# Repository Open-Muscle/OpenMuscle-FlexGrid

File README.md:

# 🧠 OpenMuscle-FlexGrid

OpenMuscle FlexGrid is a modular 60-sensor pressure-sensing platform designed for advanced forearm-based gesture tracking and biomechanical research.

This device is part of the [OpenMuscle](https://github.com/Open-Muscle) ecosystem and represents a leap forward from the original 12-sensor OM12 prototype by introducing high-density, flex-rigid PCBs and better sensor modularity.

### 📌 For documentation, firmware, and assembly guidance, visit the [OpenMuscle Hub](https://github.com/Open-Muscle/OpenMuscle-Hub).

---

## 🚀 Current revisions

**V4 (current, validated).** Fabricated at JLCPCB in June 2026 (10-unit batch, single-side SMT), brought up 2026-06-23 and in use since. Two V4 bands were assembled, flashed with [FlexGridV4-Firmware](https://github.com/Open-Muscle/FlexGridV4-Firmware) v4.0.1 and shipped as the first OpenMuscle starter kit in October 2026. V4 is the best-performing FlexGrid revision to date and the one to build. It adds an on-device **microSD card socket** for local data logging, a **discrete RGB status LED** on three PWM channels, and a reoriented slimmer board profile that hugs the forearm. It carries forward the V3 power and interconnect architecture, with the FFC tail width corrected from 11.1 mm to **10.5 mm** per the Wurth 687120183722 datasheet, the ADC matrix-row caps reduced from 2.2 uF to **100 pF** (resolves V3's 22 ms RC bleed in silicon rather than via post-fab cap removal), all resistors normalized to 0603, and several footprint cleanups. Manufacturing strategy: **single-side SMT at JLCPCB plus hand-soldering of bottom-side parts and through-hole connectors**. The design files are now at board revision **V4-2** (2026-11-03): USB presence sensing for the firmware, vias moved out of the SMD pads, USB data lines re-routed as a pair. V4-2 has not been fabricated yet, and its BOM, placement and Gerber files are still the June 2026 as-ordered set. Full status, bring-up findings and the fab checklist are in the [V4 README](KiCad/OM-FlexGrid%20V4/README.md).

**V3 (previous, validated 2026-05-13).** First revision to use a 20-pin ZIF FFC connector for the flex-to-rigid interconnect (Wurth 687120183722). Two boards populated and tested end-to-end. Sensor matrix delivers **clean single-cell press detection across all 60 sensors** with ~22% carryover decaying to noise floor within 3 columns. **V3 is the first FlexGrid generation usable as a real ML training data source.** Firmware: [FlexGridV3-Firmware v0.1.7](https://github.com/Open-Muscle/FlexGridV3-Firmware).

→ For V4 hardware files, see [`KiCad/OM-FlexGrid V4/`](KiCad/OM-FlexGrid%20V4/) and the [V4 README](KiCad/OM-FlexGrid%20V4/README.md). For V3 see [`KiCad/OM-FlexGrid V3/`](KiCad/OM-FlexGrid%20V3/) and the [V3 README](KiCad/OM-FlexGrid%20V3/README.md). Firmware: V4 bands run [FlexGridV4-Firmware](https://github.com/Open-Muscle/FlexGridV4-Firmware); V3 boards run [FlexGridV3-Firmware](https://github.com/Open-Muscle/FlexGridV3-Firmware).

| Revision | Status | Notes |
|----------|--------|-------|
| **V4** | 🟢 Validated (current) | microSD + RGB LED + slimmer reorient; 10.5 mm FFC tail; 100 pF ADC caps; fabbed 2026-06, in starter kits since 2026-10; design files at V4-2 (USB sensing, vias out of pads, USB pair; not yet fabbed) |
| **V3** | 🟢 Validated (previous) | 20-pin FFC interconnect, integrated stiffened FFC tail, ~140 Hz raw scan |
| V2 | 🟢 Tested | FFC connector exploration, fabric harness testing |
| V1 | 🟢 Tested | First production revision |
| V0 | 🟢 Tested | Original prototype |

→ Full cross-version comparison: [`KiCad/REVISIONS.md`](KiCad/REVISIONS.md). Manufacturing process used across revisions: [`docs/JLCPCB_WORKFLOW.md`](docs/JLCPCB_WORKFLOW.md).

---

## 🧬 Overview

FlexGrid uses a flexible pressure sensor matrix with rigid breakout interfaces to detect volumetric muscle contractions in real time. It supports:

- 🧠 Biomechanical signal analysis  
- 🦾 Prosthetics and exosuit research  
- 🎛️ Machine learning data pipelines  

---

## 📁 Hardware Design Files

Design files are organized by board type and version:

### 🔌 KiCad Schematics & PCB Layout

📂 [`KiCad/`](KiCad/) — all design files, organized by revision.

| Revision | Path | Description |
|----------|------|-------------|
| **V4** (current) | [`KiCad/OM-FlexGrid V4/`](KiCad/OM-FlexGrid%20V4/) | Validated. microSD socket, RGB status LED, slimmer reorient, 10.5 mm FFC tail, 100 pF ADC caps. See [V4 README](KiCad/OM-FlexGrid%20V4/README.md). |
| **V3** (previous) | [`KiCad/OM-FlexGrid V3/`](KiCad/OM-FlexGrid%20V3/) | Validated. 20-pin ZIF FFC interconnect. See [V3 README](KiCad/OM-FlexGrid%20V3/README.md). |
| V2 | [`KiCad/OM-FlexGrid V2/`](KiCad/OM-FlexGrid%20V2/) | Tested. FFC exploration + fabric harness. See [V2 README](KiCad/OM-FlexGrid%20V2/README.md). |
| V1 | [`KiCad/OM-FlexGrid V1/`](KiCad/OM-FlexGrid%20V1/) | First production revision. |
| V0 | [`KiCad/OM-FlexGrid V0/`](KiCad/OM-FlexGrid%20V0/) | Original prototype. |

Each revision folder contains both the flex (`OM-FlexGrid-Flex/`) and rigid (`OM-FlexGrid-Rigid-PCB/`) board projects, plus their gerber bundles.

---

### 📦 Bill of Materials

BOMs live next to their KiCad project for each revision:

- **V4 Rigid (JLCPCB-ready):** [`KiCad/OM-FlexGrid V4/OM-FlexGrid-Rigid-PCB/jlcpcb/production_files/BOM-OM-FlexGrid-Rigid-PCB.csv`](KiCad/OM-FlexGrid%20V4/OM-FlexGrid-Rigid-PCB/jlcpcb/production_files/BOM-OM-FlexGrid-Rigid-PCB.csv) (LCSC part numbers, machine-readable, generated by the JLCPCB KiCad plugin). This is the June 2026 as-ordered V4 set; the V4-2 additions (R19, R20, R21) are not in it yet. The hand-soldered parts list (microSD socket, FFC connector, battery JST, pin headers, plus single-side-strategy BOT-side SMT) is documented prose-style in the [V4 README](KiCad/OM-FlexGrid%20V4/README.md#hand-soldered-parts-full-list).
- **V3 Rigid:** [`KiCad/OM-FlexGrid V3/OM-FlexGrid-Rigid-PCB/OM-FlexGrid-Rigid-PCB.csv`](KiCad/OM-FlexGrid%20V3/OM-FlexGrid-Rigid-PCB/OM-FlexGrid-Rigid-PCB.csv) (KiCad export).
- **Flex (V3 and V4):** no electronic-component BOM. The flex tail integrates the FFC connector pads directly; the only off-board parts are the Velostat sheet and the mating Wurth 687120183722 connector populated on the rigid board.

Older revision BOMs are kept under [`BOM/`](BOM/) for history.

---

### 🛠 Assembly & Testing

For V4: the [build video](https://youtu.be/2tb6GW4FNU0) covers hand-soldering the parts JLCPCB does not populate, [BRINGUP.md](https://github.com/Open-Muscle/FlexGridV4-Firmware/blob/main/BRINGUP.md) in the firmware repo covers flashing, and the [band reference](https://github.com/Open-Muscle/FlexGridV4-Firmware/blob/main/docs/device-reference.md) explains every button and light pattern. Recording, training and inference software lives in [OpenMuscle-Software](https://github.com/Open-Muscle/OpenMuscle-Software). For the wider picture see the [OpenMuscle Hub](https://github.com/Open-Muscle/OpenMuscle-Hub) and the videos on [YouTube Open Muscle](https://youtube.com/@openmuscle) or [TURFPTAx Youtube](https://youtube.com/@turfptax).

---

## 🤝 Contributions

We welcome improvements to sensor design, firmware, or real-world testing. Please fork the repo and submit pull requests!

---
**Open Muscle** is an open-source prosthetic sensor initiative designed for accessibility, innovation, and community collaboration.

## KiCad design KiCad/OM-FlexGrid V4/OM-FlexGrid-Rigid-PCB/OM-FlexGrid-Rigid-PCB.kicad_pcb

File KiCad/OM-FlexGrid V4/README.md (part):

# OM-FlexGrid V4

> **Status: VALIDATED, CURRENT REVISION.** Brought up 2026-06-23 from the 10-unit JLCPCB batch and in use since. Two bands were assembled, flashed with [FlexGridV4-Firmware](https://github.com/Open-Muscle/FlexGridV4-Firmware) v4.0.1 and shipped as the first OpenMuscle starter kit in October 2026. V4 is the best-performing FlexGrid revision to date. Two hardware bugs surfaced during bring-up: USBLC6 ESD chip pinout reversed in the schematic (fixed in the schematic; the June boards work with a 180-degree chip rotation), and the as-ordered IMU is a TOKMAS rebrand rather than genuine InvenSense as planned (driver auto-probes both variants; see [Bring-up findings](#bring-up-findings-2026-06-23) below). Total landed cost $341.84 for 10 units (~$35 per board for the JLC half; see [Cost breakdown](#cost-breakdown-10-unit-batch-june-2026) for per-unit details).
>
> **Design files are at revision V4-2 (2026-11-03).** V4-2 adds USB presence sensing, moves the vias out of the SMD pads and re-routes the USB data lines as a pair; see [Revision V4-2](#revision-v4-2-2026-11-03). V4-2 has not been fabricated. The BOM, CPL and Gerber files under `jlcpcb/` and `production/` are still the June 2026 as-ordered V4 set and must be regenerated before the next order.

## 🎬 Build video

[**Unboxing & Setup: assembling the FlexGrid V4**](https://youtu.be/2tb6GW4FNU0) walks through hand-soldering the parts JLCPCB does not populate (ESP32-S3 module, CD74HC4067 mux, ZIF/FFC connector, USB-C, buttons, RGB LED), the USBLC6 180-degree rotation fix, and first power-on with the flex sensor mated. The microSD socket and haptic parts are deferred to a future video.

## 📄 Design documents (PDFs)

For people who want to review the design without opening KiCad:

### Rigid PCB

- 📐 [`FlexGridV4-Rigid-Schematic.pdf`](OM-FlexGrid-Rigid-PCB/FlexGridV4-Rigid-Schematic.pdf): full schematic, all sheets, all nets named
- 🟦 [`FlexGridV4-Rigid-PCB.pdf`](OM-FlexGrid-Rigid-PCB/FlexGridV4-Rigid-PCB.pdf): board layout

### Flex PCB

- 📐 [`FlexGridV4-Flex-Schematic.pdf`](OM-FlexGrid-Flex/FlexGridV4-Flex-Schematic.pdf): sensor matrix schematic
- 🟦 [`FlexGridV4-Flex-PCB.pdf`](OM-FlexGrid-Flex/FlexGridV4-Flex-PCB.pdf): flex layout including the stiffened FFC tail
- 🟧 [`FrontCopper_SolderMask.pdf`](OM-FlexGrid-Flex/FrontCopper_SolderMask.pdf): front-side copper + soldermask overlay (useful for sanity-checking the Velostat sensor cell exposures)

### What gets populated and what doesn't

The split between "JLCPCB assembles this" and "I hand-solder this after the boards arrive" is documented in [Hand-soldered parts (full list)](#hand-soldered-parts-full-list) below. tl;dr:

- **JLCPCB assembles all TOP-side SMT parts** (passives, regulators, charger, MUX-driver MOSFETs, MAX16054, USBLC6, IMU, CHRG LED, RGB LED, etc.)
- **You hand-solder everything else**: all BOT-side SMT (including U1 CD74HC4067 mux and U2 ESP32-S3 module), the microSD socket, the Wurth FFC connector, USB-C, and every through-hole pin header / JST. The per-designator table further down has each part listed by reference designator with solder-difficulty notes.

Fourth major revision of the Open Muscle FlexGrid wearable sensor platform. V4 builds on the V3 production baseline (which validated the FFC interconnect and proved the 60-cell matrix as a usable ML training data source) and adds on-device storage, a status indicator, and a slimmer board profile.

---

## Bring-up findings (2026-06-23)

Two boards from the 10-unit fab batch were flashed with V4 MicroPython firmware ([Open-Muscle/FlexGridV4-Firmware](https://github.com/Open-Muscle/FlexGridV4-Firmware), see its `BRINGUP.md` for step-by-step flashing instructions). Both ran the OpenMuscle discovery + subscribe protocol end-to-end against the PC `openmuscle web` app and the Android Connect client. Two hardware bugs surfaced during bring-up; both are documented here so future builders do not re-discover them.

### 1. USBLC6-2SC6 pinout reversed in schematic (FIXED)

The V4 KiCad schematic wired the USBLC6 with pin 2 on VBUS and pin 5 on GND. The actual chip pinout is the other way around (pin 2 = GND, pin 5 = VCC). With the silkscreen-correct placement, USB enumerates VBUS only (Windows reports "Device Descriptor Request Failed"), no COM port appears.

- **Workaround for the existing 10-unit batch:** rotate the USBLC6 chip 180 degrees from the silkscreen orientation during placement. The SOT-23-6 footprint is symmetric so the I/O pin pairs still route correctly, and VCC and GND land where they belong.
- **Schematic fix landed** in this repo. The next fab order will be correct without rotation.

### 2. IMU is a TOKMAS rebrand, not genuine InvenSense (DRIVER WORKAROUND)

The pre-fab checklist documented the IMU choice as genuine InvenSense ICM-42688-P (LCSC C1850418). The as-ordered BOM ended up with the cheaper TOKMAS rebrand (LCSC C54308212) instead. TOKMAS has the same general silicon spec but a different I2C address (0x36 / 0x37 instead of 0x68 / 0x69) and a different register map (data at 0x00-0x0D instead of 0x1F-0x2A).

- **Workaround:** [`lib/imu.py`](https://github.com/Open-Muscle/FlexGridV4-Firmware/blob/main/lib/imu.py) in the V4 firmware auto-probes both variants. Verified working on board #1: live accel + gyro at the expected rates.
- **Recommendation for the next fab order:** switch back to genuine InvenSense (C1850418) and retire the TOKMAS code path. The ~$11 per-chip savings cost a custom driver branch and ongoing maintenance.

### Firmware repo and bring-up guide

- Firmware: [Open-Muscle/FlexGridV4-Firmware](https://github.com/Open-Muscle/FlexGridV4-Firmware)
- Step-by-step flashing instructions: [`BRINGUP.md`](https://github.com/Open-Muscle/FlexGridV4-Firmware/blob/main/BRINGUP.md)
- One-shot flash script: `flash.py COM<port>` after pip-installing esptool 5.x + mpremote and downloading the MicroPython binary

---

## Revision V4-2 (2026-11-03)

Schematic and layout changes made after the first production run. These live in the KiCad files only: nothing at V4-2 has been fabricated, and the `jlcpcb/` and `production/` outputs are still the June 2026 as-ordered set. Rev field in the schematic title block: `V4-2`.

### USB presence sensing (new)

The June boards cannot tell whether USB is plugged in. The MAX16054 latch keeps the board powered while VBUS is present, so the power button appears to do nothing on USB and the firmware has no way to know why (see the [band reference](https://github.com/Open-Muscle/FlexGridV4-Firmware/blob/main/docs/device-reference.md) in the firmware repo). V4-2 adds a VBUS divider the ESP32-S3 can read.

| Designator | Value | Footprint | Between | Role |
|---|---|---|---|---|
| R19 | 10k | 0603 | VBUS and `VBUS-STAT` | high side of the VBUS sense divider |
| R20 | 100k | 0603 | `VBUS-STAT` and GND | low side of the divider |
| R21 | 100k | 0603 | `PWR_OFF` and GND | pull-down on the Q3 gate (IO45) so the power-off MOSFET stays off while the ESP32 boots |

`VBUS-STAT` lands on U2 pin 32 (IO39). **Value check still open:** as drawn, 10k over 100k puts about 4.5 V on IO39 with 5 V on VBUS, above the ESP32-S3 GPIO limit. Pick values that keep the node under 3.3 V (for example 100k over 100k for 2.5 V) before the next fab. Firmware support for reading the pin is not written yet.

The charger PROG note on the schematic was also corrected: R4 is 2k on the STC4054 PROG pin, which sets the charge current to 500 mA (the old note suggesting 2.7k was stale).

### Vias moved out of the pads ([#3](https://github.com/Open-Muscle/OpenMuscle-FlexGrid/issues/3))

The June layout had 29 vias sitting inside SMD pads (ESP32 module pads, mux, LDO, charger, buttons, microSD socket, several resistors). An unplugged via inside a pad wicks solder away from the joint during reflow. V4-2 moves them next to their pads instead. One remains, on Q3 pad 2 (GND, source of the power-off MOSFET), where the via annulus still overlaps the pad edge.

### USB data lines routed as a pair ([#4](https://github.com/Open-Muscle/OpenMuscle-FlexGrid/issues/4))

The June layout ran D+ and D- between the USBLC6 and the ESP32 module as two unrelated traces, 15.6 mm and 34.5 mm long. V4-2 routes them together: 16.4 mm and 19.6 mm, 0.2 mm wide, 0.25 mm edge gap where they run side by side, one layer change each; the connector-to-ESD segments are 7.6 mm and 7.3 mm. The pair uses the default net class geometry and has not been checked against the JLCPCB 4-layer stack-up for 90 ohm differential impedance. The ESP32-S3 is a USB full-speed device (12 Mbit/s), so over this length the change is about tidiness and skew rather than a hard signal-integrity requirement.

---

## What is new in V4 vs V3

| Area | V3 | V4 | Why |
|---|---|---|---|
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
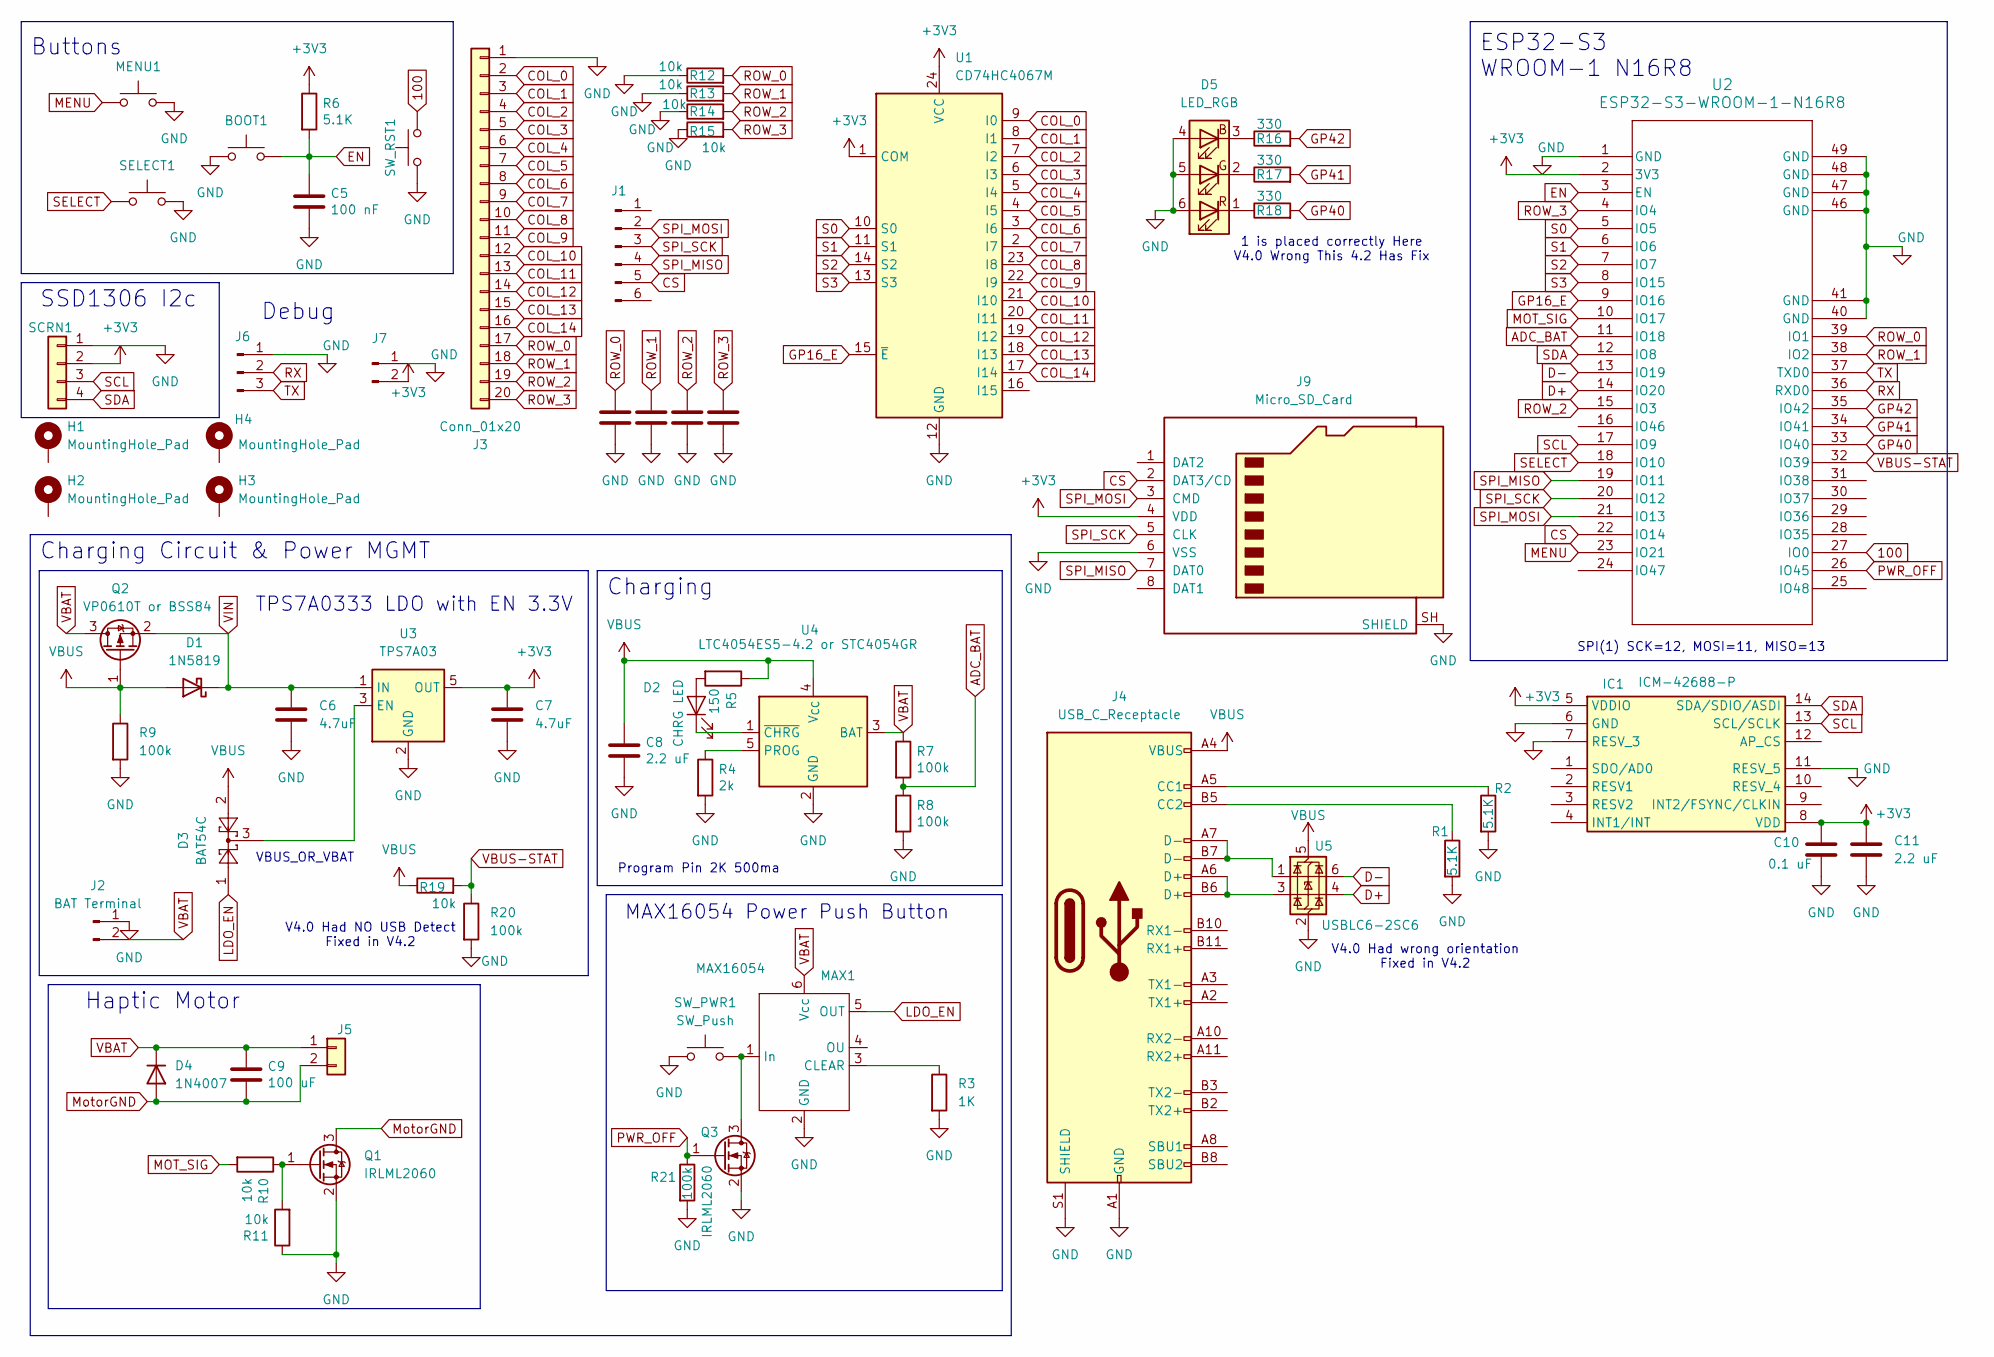
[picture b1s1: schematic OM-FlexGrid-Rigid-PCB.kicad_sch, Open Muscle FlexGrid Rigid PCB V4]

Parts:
BOOT1: SW_Push; EVQP2P02M; LCSC C512395
C5: 100 nF; C_0603_1608Metric; JLCPN C1525
C6, C7: 4.7uF; C_0805_2012Metric; LCSC C1779
C8: 2.2 uF; C_0603_1608Metric; JLCPN C12530
C9: 100 uF; C_0603_1608Metric; JLCPN C12530
C10: 0.1 uF; C_0603_1608Metric; LCSC C14663
C11: 2.2 uF; C_0603_1608Metric; LCSC C23630
C12, C13, C14, C15: 100 pF; C_0603_1608Metric; JLCPN C12530
D1: 1N5819; D_SOD-123; LCSC C64885
D2: CHRG LED; LED_0805_2012Metric; JLCPN C72043
D3: BAT54C; SOT-23; LCSC C22466350
D4: 1N4007; D_SOD-123; LCSC C22440662
D5: LED_RGB; LED_RGB_PLCC-6; LCSC C2827305
H1, H2, H3, H4: MountingHole_Pad; MountingHole_2.2mm_M2
IC1: ICM-42688-P; LGA-14_3x2.5mm_P0.5mm_LayoutBorder3x4y; Mouser Part Number 410-ICM-42688-P
J1: Conn_01x06_Pin; PinHeader_2x03_P1.27mm_Vertical
J2: BAT Terminal; PinHeader_1x02_P2.54mm_Vertical
J3: Conn_01x20; 687120183722-20P-Bottom
J4: USB_C_Receptacle; USB_C_Receptacle_HRO_TYPE-C-31-M-12
J5: Conn_01x02; PinHeader_1x02_P2.00mm_Vertical
J6: Conn_01x03_Pin; PinHeader_1x03_P2.54mm_Vertical
J7: Conn_01x02_Pin; PinSocket_1x02_P2.00mm_Vertical
J9: Micro_SD_Card; CONN_503398-1892_MOL
MAX1: MAX16054; TSOT-23-6; LCSC C79401
MENU1: SW_Push; EVQP2P02M; LCSC C512395
Q1, Q3: IRLML2060; SOT-23; LCSC C67275
Q2: VP0610T or BSS84; SOT-23; LCSC C8492
R1, R2, R6: 5.1K; R_0603_1608Metric; JLCPN C25905
R3: 1K; R_0603_1608Metric; LCSC C21190
R4: 2k; R_0603_1608Metric; JLCPN C25905
R5: 150; R_0603_1608Metric; JLCPN C4109
R7, R8: 100k; R_0603_1608Metric; JLCPN C25905
R9, R20, R21: 100k; R_0603_1608Metric; LCSC C25803
R10, R11: 10k; R_0603_1608Metric; JLCPN C25744
R12, R13, R14, R15, R19: 10k; R_0603_1608Metric; JLCPN C25905
R16, R17, R18: 330; R_0603_1608Metric; JLCPN C25905
SCRN1: Conn_01x04; PinHeader_1x04_P2.54mm_Vertical
SELECT1: SW_Push; EVQP2P02M; LCSC C512395
SW_PWR1: SW_Push; EVQP2P02M; LCSC C512395
SW_RST1: SW_Push; EVQP2P02M; LCSC C512395
U1: CD74HC4067M; TSSOP-24_4.4x7.8mm_P0.65mm
U2: ESP32-S3-WROOM-1-N16R8
U3: TPS7A03; SOT-23-5; LCSC C2873330
U4: LTC4054ES5-4.2 or STC4054GR; TSOT-23-5; LCSC C262930
U5: USBLC6-2SC6; SOT-23-6; LCSC C2687116

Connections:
100: SW_RST1.2, U2.27 (IO0)
+3V3: C7.1, C10.1, C11.1, IC1.5 (VDDIO), IC1.8 (VDD), J7.2, J9.4 (VDD), R6.1, SCRN1.2, U1.1 (COM), U1.24 (VCC), U2.2 (3V3), U3.5 (OUT)
ADC_BAT: R7.2, R8.1, U2.11 (IO18)
COL_0: J3.2, U1.9 (I0)
COL_1: J3.3, U1.8 (I1)
COL_2: J3.4, U1.7 (I2)
COL_3: J3.5, U1.6 (I3)
COL_4: J3.6, U1.5 (I4)
COL_5: J3.7, U1.4 (I5)
COL_6: J3.8, U1.3 (I6)
COL_7: J3.9, U1.2 (I7)
COL_8: J3.10, U1.23 (I8)
COL_9: J3.11, U1.22 (I9)
COL_10: J3.12, U1.21 (I10)
COL_11: J3.13, U1.20 (I11)
COL_12: J3.14, U1.19 (I12)
COL_13: J3.15, U1.18 (I13)
COL_14: J3.16, U1.17 (I14)
CS: J1.5, J9.2 (DAT3/CD), U2.22 (IO14)
D+: U2.14 (IO20), U5.4 (I/O2)
D-: U2.13 (IO19), U5.6 (I/O1)
EN: BOOT1.2, C5.2, R6.2, U2.3 (EN)
GND: BOOT1.1, C5.1, C6.2, C7.2, C8.1, C10.2, C11.2, C12.1, C13.1, C14.1, C15.1, D5.4 (BA), D5.5 (GA), D5.6 (RA), IC1.6 (GND), IC1.7 (RESV_3), IC1.11 (RESV_5), J2.1, J3.1, J4.A1 (GND), J4.A12 (GND), J4.B1 (GND), J4.B12 (GND), J4.S1 (SHIELD), J6.1, J7.1, J9.6 (VSS), J9.SH (SHIELD), MAX1.2 (GND), MENU1.2, Q1.2 (S), Q3.2 (S), R1.2, R2.2, R3.2, R4.2, R8.2, R9.2, R11.1, R12.1, R13.1, R14.1, R15.1, R20.2, R21.2, SCRN1.1, SELECT1.2, SW_PWR1.1, SW_RST1.1, U1.12 (GND), U2.1 (GND), U2.40 (GND), U2.41 (GND), U2.46 (GND), U2.47 (GND), U2.48 (GND), U2.49 (GND), U3.2 (GND), U4.2 (GND), U5.2 (GND)
GP16_E: U1.15 (~E), U2.9 (IO16)
GP40: R18.2, U2.33 (IO40)
GP41: R17.2, U2.34 (IO41)
GP42: R16.2, U2.35 (IO42)
LDO_EN: D3.1, MAX1.5 (OUT)
MENU: MENU1.1, U2.23 (IO21)
MOT_SIG: R10.2, U2.10 (IO17)
MotorGND: C9.1, D4.2 (A), J5.2, Q1.3 (D)
unnamed: D2.2 (A), R5.2
unnamed: D2.1 (K), U4.1 (~CHRG)
unnamed: D5.3 (BK), R16.1
unnamed: D5.2 (GK), R17.1
unnamed: D5.1 (RK), R18.1
unnamed: J4.A5 (CC1), R2.1
unnamed: J4.B5 (CC2), R1.1
unnamed: J4.A6 (D+), J4.B6 (D+), U5.3 (I/O2)
unnamed: J4.A7 (D-), J4.B7 (D-), U5.1 (I/O1)
unnamed: MAX1.3 (CLEAR), R3.1
unnamed: MAX1.1 (In), Q3.3 (D), SW_PWR1.2
unnamed: Q1.1 (G), R10.1, R11.2
unnamed: D3.3, U3.3 (EN)
unnamed: R4.1, U4.5 (PROG)
PWR_OFF: Q3.1 (G), R21.1, U2.26 (IO45)
ROW_0: C12.2, J3.17, R12.2, U2.39 (IO1)
ROW_1: C13.2, J3.18, R13.2, U2.38 (IO2)
ROW_2: C14.2, J3.19, R14.2, U2.15 (IO3)
ROW_3: C15.2, J3.20, R15.2, U2.4 (IO4)
RX: J6.2, U2.36 (RXD0)
S0: U1.10 (S0), U2.5 (IO5)
S1: U1.11 (S1), U2.6 (IO6)
S2: U1.14 (S2), U2.7 (IO7)
S3: U1.13 (S3), U2.8 (IO15)
SCL: IC1.13 (SCL/SCLK), SCRN1.3, U2.17 (IO9)
SDA: IC1.14 (SDA/SDIO/ASDI), SCRN1.4, U2.12 (IO8)
SELECT: SELECT1.1, U2.18 (IO10)
SPI_MISO: J1.4, J9.7 (DAT0), U2.19 (IO11)
SPI_MOSI: J1.2, J9.3 (CMD), U2.21 (IO13)
SPI_SCK: J1.3, J9.5 (CLK), U2.20 (IO12)
TX: J6.3, U2.37 (TXD0)
VBAT: C9.2, D4.1 (K), J2.2, J5.1, MAX1.6 (Vcc), Q2.3 (D), R7.1, U4.3 (BAT)
VBUS: C8.2, D1.2 (A), D3.2, J4.A4 (VBUS), J4.A9 (VBUS), J4.B4 (VBUS), J4.B9 (VBUS), Q2.1 (G), R5.1, R9.1, R19.1, U4.4 (V_{CC}), U5.5 (VBUS)
VBUS-STAT: R19.2, R20.1, U2.32 (IO39)
VIN: C6.1, D1.1 (K), Q2.2 (S), U3.1 (IN)

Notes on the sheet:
Charging Circuit & Power MGMT
Haptic Motor
V4.0 Had NO USB Detect Fixed in V4.2
Buttons
ESP32-S3 WROOM-1 N16R8
1 is placed correctly Here V4.0 Wrong This 4.2 Has Fix
TPS7A0333 LDO with EN 3.3V
SPI(1) SCK=12, MOSI=11, MISO=13
SSD1306 I2c
Program Pin 2K 500ma
MAX16054 Power Push Button
VBUS_OR_VBAT
V4.0 Had wrong orientation Fixed in V4.2
Charging
Debug

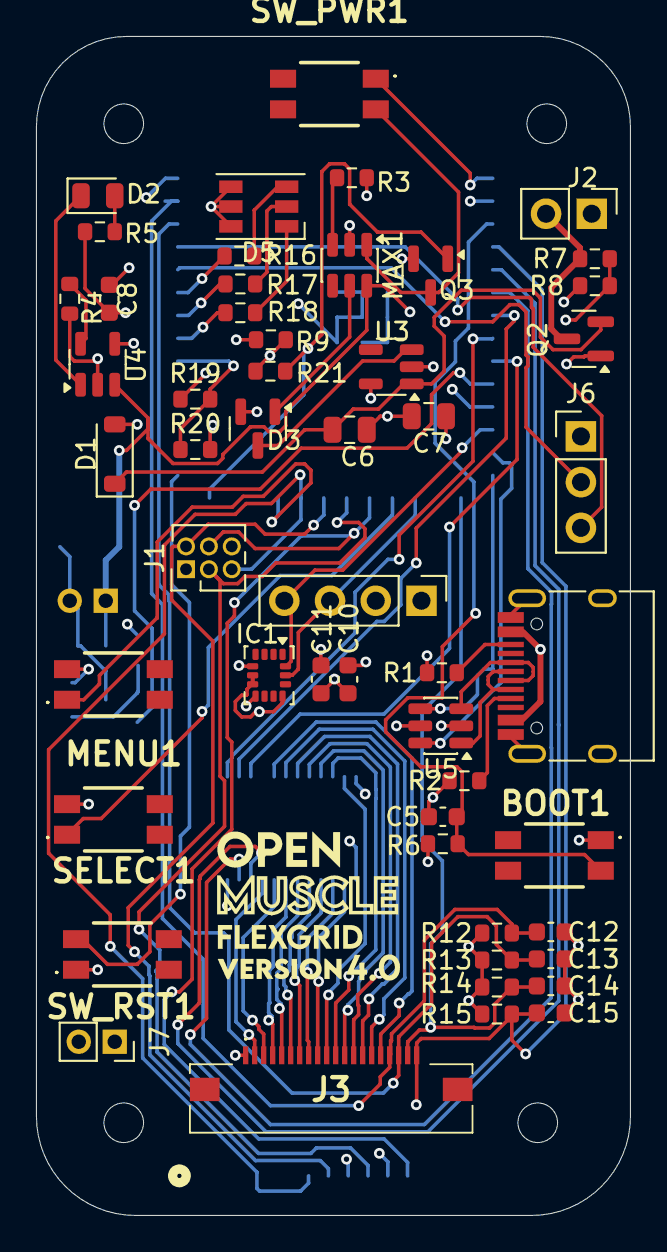
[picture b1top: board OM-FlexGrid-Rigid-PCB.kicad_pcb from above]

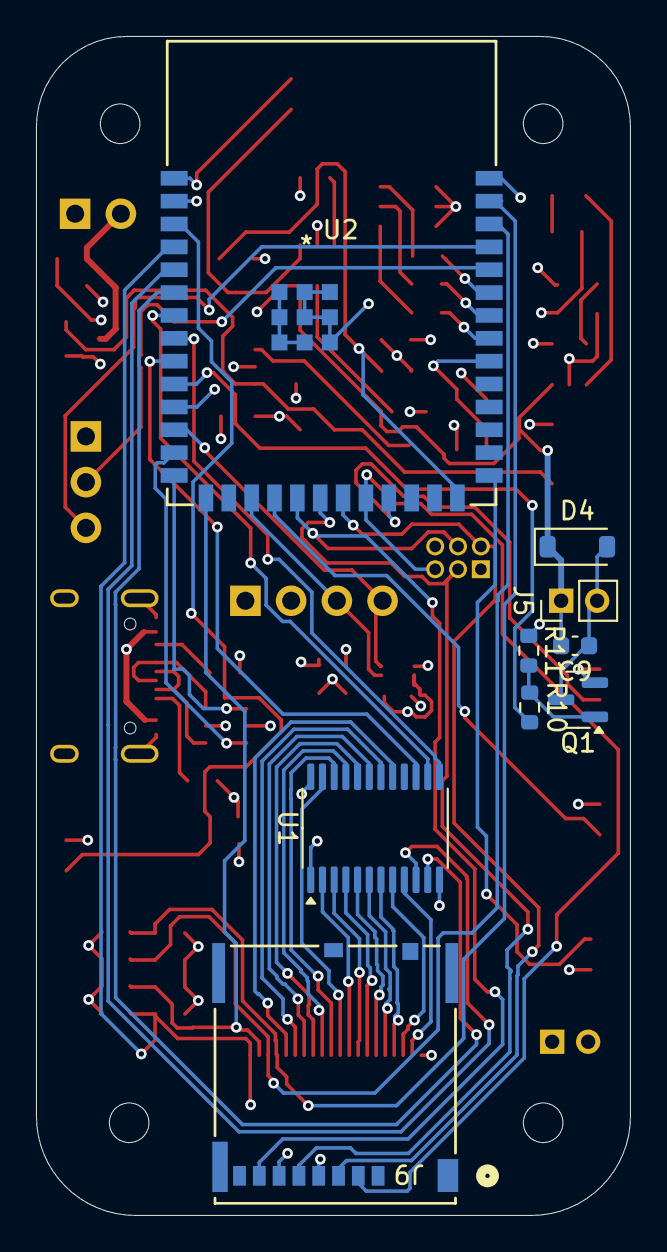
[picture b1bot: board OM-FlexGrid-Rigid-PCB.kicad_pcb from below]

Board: 4 copper layers, 33.0 x 65.5 mm, 65 parts (9 on the bottom side), 66 nets.

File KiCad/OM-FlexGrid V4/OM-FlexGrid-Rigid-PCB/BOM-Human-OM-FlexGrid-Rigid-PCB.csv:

"Id";"Designator";"Footprint";"Quantity";"Designation";"Supplier and ref";
1;"BOOT1, MENU1, SELECT1, SW_PWR1, SW_RST1";"EVQP2P02M";5;"SW_Push";;;
2;"C5";"C_0603_1608Metric";1;"100 nF";;;
3;"C6, C7";"C_0805_2012Metric";2;"4.7uF";;;
4;"C8, C11, C12, C13, C14, C15";"C_0603_1608Metric";6;"2.2 uF";;;
5;"C10";"C_0603_1608Metric";1;"0.1 uF";;;
6;"D1";"D_SOD-123";1;"1N5819";;;
7;"D2";"LED_0805_2012Metric";1;"CHRG LED";;;
8;"D3";"SOT-23";1;"BAT54C";;;
9;"D5";"LED_RGB_PLCC-6";1;"LED_RGB";;;
10;"IC1";"LGA-14_3x2.5mm_P0.5mm_LayoutBorder3x4y";1;"ICM-42688-P";;;
11;"MAX1";"SOT-23-6";1;"~";;;
12;"Q2";"SOT-23";1;"VP0610T or BSS84";;;
13;"Q3";"SOT-23";1;"IRLML2060";;;
14;"R1, R2, R6";"R_0603_1608Metric";3;"5.1K";;;
15;"R3";"R_0603_1608Metric";1;"1K";;;
16;"R4";"R_0603_1608Metric";1;"2k";;;
17;"R5";"R_0603_1608Metric";1;"150";;;
18;"R7, R8, R9";"R_0603_1608Metric";3;"100k";;;
19;"R12, R13, R14, R15";"R_0603_1608Metric";4;"10k";;;
20;"R16, R17, R18";"R_0603_1608Metric";3;"330";;;
21;"SCRN1";"PinHeader_1x04_P2.54mm_Vertical";1;"Conn_01x04";;;
22;"U3";"SOT-23-5";1;"TPS7A03";;;
23;"U4";"TSOT-23-5";1;"LTC4054ES5-4.2 or STC4054GR";;;
24;"U5";"SOT-23-6";1;"USBLC6-2SC6";;;

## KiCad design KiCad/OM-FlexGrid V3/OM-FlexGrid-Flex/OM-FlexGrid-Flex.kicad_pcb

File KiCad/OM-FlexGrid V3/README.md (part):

# OM-FlexGrid V3

> **Status: PRODUCTION-QUALITY MATRIX (as of 2026-05-13).** Two boards populated and brought up end-to-end. The Wurth 687120183722 FFC interconnect mates cleanly with the integrated stiffened flex tail (0.20 mm FR4 stiffener, bottom-side, total ~0.31 mm — on Wurth's 0.30 ±0.05 mm spec). Sensor matrix delivers **clean single-cell press detection across all 60 sensors** — peak ~1100 ADC counts on direct press, 22% carryover to the next column, decaying to the noise floor within 3 columns. Idle baseline is exactly 0. Scan rate 59 Hz. UDP telemetry over Wi-Fi confirmed reaching the desktop visualizer (`openmuscle web` and `openmuscle receive`). **The matrix is now usable as a real ML training data source — for the first time in the project's history.**
>
> Firmware that makes this work lives at [Open-Muscle/FlexGridV3-Firmware](https://github.com/Open-Muscle/FlexGridV3-Firmware) (v0.1.7, MIT). Six non-obvious scan techniques were needed; they're documented in that repo's `README` under "Sensor scan techniques".
>
> Open items: characterizing one occasionally-glitchy sensor on board #1; diagnosing IO2 (= ROW_1) GPIO-output anomaly on board #1 (suspect R13 or its trace); ICM-42688-P IMU driver still TODO; software baseline subtraction may further reduce the 22% carryover toward <5%.

Third major revision of the Open Muscle FlexGrid wearable sensor platform. V3 standardizes the flex-to-rigid interconnect on a 20-pin 0.5 mm-pitch ZIF FFC connector, eliminating the hand-soldered pin-header link used through V2.

---

## Overview

V3 is two paired PCBs, mated by a single FFC ribbon formed by the flex PCB's own tail.

| Board | Role | Layers | Mating |
|-------|------|--------|--------|
| **OM-FlexGrid-Flex** | 15×4 Velostat sensor matrix on a flex PCB. The PCB tail itself is the male FFC. | 2L flex | Inserts into J3 on rigid |
| **OM-FlexGrid-Rigid-PCB** | ESP32-S3 controller, mux, power, display, IMU. | 4L rigid (1.6 mm) | Hosts J3 = Wurth 687120183722 |

---

## Flex-to-Rigid Interconnect (NEW IN V3)

The flex PCB tail is fabricated with 20 exposed gold pads on the top copper layer (F.Cu) and a stiffener on the bottom. It plugs directly into the Wurth ZIF connector on the rigid board — no separate FFC cable.

### Connector (rigid side, J3)

| Field | Value |
|-------|-------|
| Manufacturer P/N | **Wurth 687120183722** |
| Mouser P/N | 710-687120183722 |
| Series | WR-FPC SMT ZIF Horizontal Low Profile |
| Pin count | 20 |
| Pitch | 0.50 mm |
| Contact orientation | **Bottom Contact** |
| Actuator | Flip-lock ZIF (top) |
| Operating temp | -25 °C to +85 °C |
| Datasheet | https://www.we-online.com/components/products/datasheet/687120183722.pdf |

"Bottom Contact" means the connector's contacts are on the underside of the housing, so **the FFC's contact pads must face the rigid PCB when inserted.**

### FFC tail (flex side, J1) — design spec

The tail is integral to the flex PCB; there is no separate FFC cable.

| Parameter | Value | Source |
|-----------|-------|--------|
| Pin count | 20 | matches J3 |
| Pitch | 0.50 mm | Wurth datasheet |
| Contact pad width | 0.30 mm | Wurth datasheet |
| Exposed contact length | 1.45 mm (min) | Wurth datasheet |
| Pin-to-pin span (centre of pin 1 → pin 20) | 9.50 mm | 19 × 0.5 mm |
| Tail width across pads | ≥ 11.10 mm | Pl + 2× 0.80 mm end margin |
| Insertion depth into housing | ~3.8 mm | Wurth datasheet |
| **Total FFC tail thickness** (flex + stiffener) | **0.30 mm ±0.05 mm** | Wurth datasheet |
| Contacts on layer | **F.Cu** (top) — must face down on insertion | KiCad project |
| Stiffener side | **B side** (opposite contacts) | required by Wurth |
| Plating | ENIG (gold) recommended | reliable mating |

### Orientation gotcha

Because the rigid connector is bottom-contact and the FFC pads are on F.Cu (top side of flex):

- During use the flex tail must enter J3 with **F.Cu facing the rigid board**.
- In the wearable, the sensor matrix sits on top of the forearm with sensor pads up; the tail folds 180° beneath the matrix and its contacts naturally end up facing down — which is what we want. Verify in the 3D view before sending to fab.

---

## Flex PCB Fabrication (JLCPCB)

These are the order parameters for JLCPCB's flex PCB service. Cross-check against `OM-FlexGrid-Flex/V2-1 Gerber.zip` (current latest) before submitting.

| Parameter | Value |
|-----------|-------|
| Layers | 2 |
| Material | Polyimide flex |
| Base thickness | 0.11 mm (JLCPCB default 2L) |
| Coverlay | Yellow polyimide (default) |
| Surface finish | **ENIG** (required for reliable FFC mating; HASL will not work) |
| Copper weight | 1 oz (0.5 oz also fine) |
| **Stiffener material** | **FR4** |
| **Stiffener thickness** | **0.20 mm** |
| **Stiffener side** | **Bottom** (opposite the FFC contacts) |
| Stiffener placement | Drawn on `User.1 (Stiffener)` layer in KiCad |
| EMI shielding | None |
| 3M tape backing | Optional (none required for FFC) |

**Total FFC tail thickness = 0.11 mm flex + 0.20 mm stiffener ≈ 0.31 mm** ✓ within Wurth's 0.30 ±0.05 mm window.

### Stiffener outline rules

The stiffener is a rectangular FR4 backer bonded to the bottom side of the flex tail. JLCPCB needs an outline drawn on a dedicated layer so they know where to glue it.

- Layer: `User.1` (already named "Stiffener" in `OM-FlexGrid-Flex.kicad_pcb`).
- Shape: rectangle covering the **full width of the FFC tail** and extending from the **board edge** at least **5 mm past the last contact pad** (≈ 7 mm total length is typical). This puts the entire ZIF clamp area on stiffener.
- Do not let the stiffener cross the bend region of the flex — keep it confined to the tail.
- When uploading to JLCPCB, in the order form select stiffener side = **Bottom side**, material = **FR4**, thickness = **0.2 mm**.

### Notes on the current J1 footprint

`OpenMuscleDevKit:20Pin-FFC` (used as J1) has 20 pads at 0.5 mm pitch, 0.30 × 2.60 mm each, on F.Cu — geometry matches Wurth's recommended FFC pattern. Two items to confirm before fab:

1. **Soldermask opening** on the contact area should match or exceed the 1.45 mm exposed-contact length (KiCad's mask expansion typically handles this; verify in F.Mask).
2. **Stiffener layer is currently empty** — there is no shape drawn on `User.1`. You need to add a rectangle there before generating new gerbers, otherwise JLCPCB has no stiffener outline to follow. The previous V2-1 gerber already includes `OM-FlexGrid-Flex-Stiffener.gbr`, so the stiffener was authored as a separate file last round; either re-import it onto User.1 or redraw it.

---

## Rigid PCB

4-layer, 1.6 mm, ESP32-S3 host. No architectural changes from V2. See `OM-FlexGrid-Rigid-PCB/OM-FlexGrid-Rigid-PCB.csv` for the full BOM.

### Key components

| Ref | Component | Function |
|-----|-----------|----------|
| U? | ESP32-S3-WROOM-1-N16R8 | MCU (16 MB Flash, 8 MB PSRAM) |
| MUX | CD74HC4067 | 16:1 analog mux (15 columns used) |
| OLED | SSD1306 128×32 | I²C status display |
| IC1 | ICM-42688-P | 6-DOF IMU (I²C, optional) |
| MAX1 | MAX16054 | Soft power latch |
| — | TPS7A0333 | 3.3 V LDO |
| — | LTC4054ES5 | Single-cell LiPo charger |
| Q1, Q3 | IRLML2060 | Haptic motor / aux MOSFET |
| **J3** | **Wurth 687120183722** | **20-pin ZIF, FFC to flex matrix** |
| J4 | USB-C (HRO TYPE-C-31-M-12) | Charge / programming |

### Sensor matrix scan

CD74HC4067 walks 15 columns to 3.3 V one at a time; four row lines with 10 kΩ pulldowns are sampled on ESP32 ADC1. 60 readings per scan frame.

---

## Bring-up findings (2026-05-13)

Five firmware-side issues had to be solved before the matrix produced clean data. They're all documented in detail in the [firmware repo's README](https://github.com/Open-Muscle/FlexGridV3-Firmware#sensor-scan-techniques), but the hardware-relevant takeaways are:

| Issue | Root cause | Where the fix lives |
|---|---|---|
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
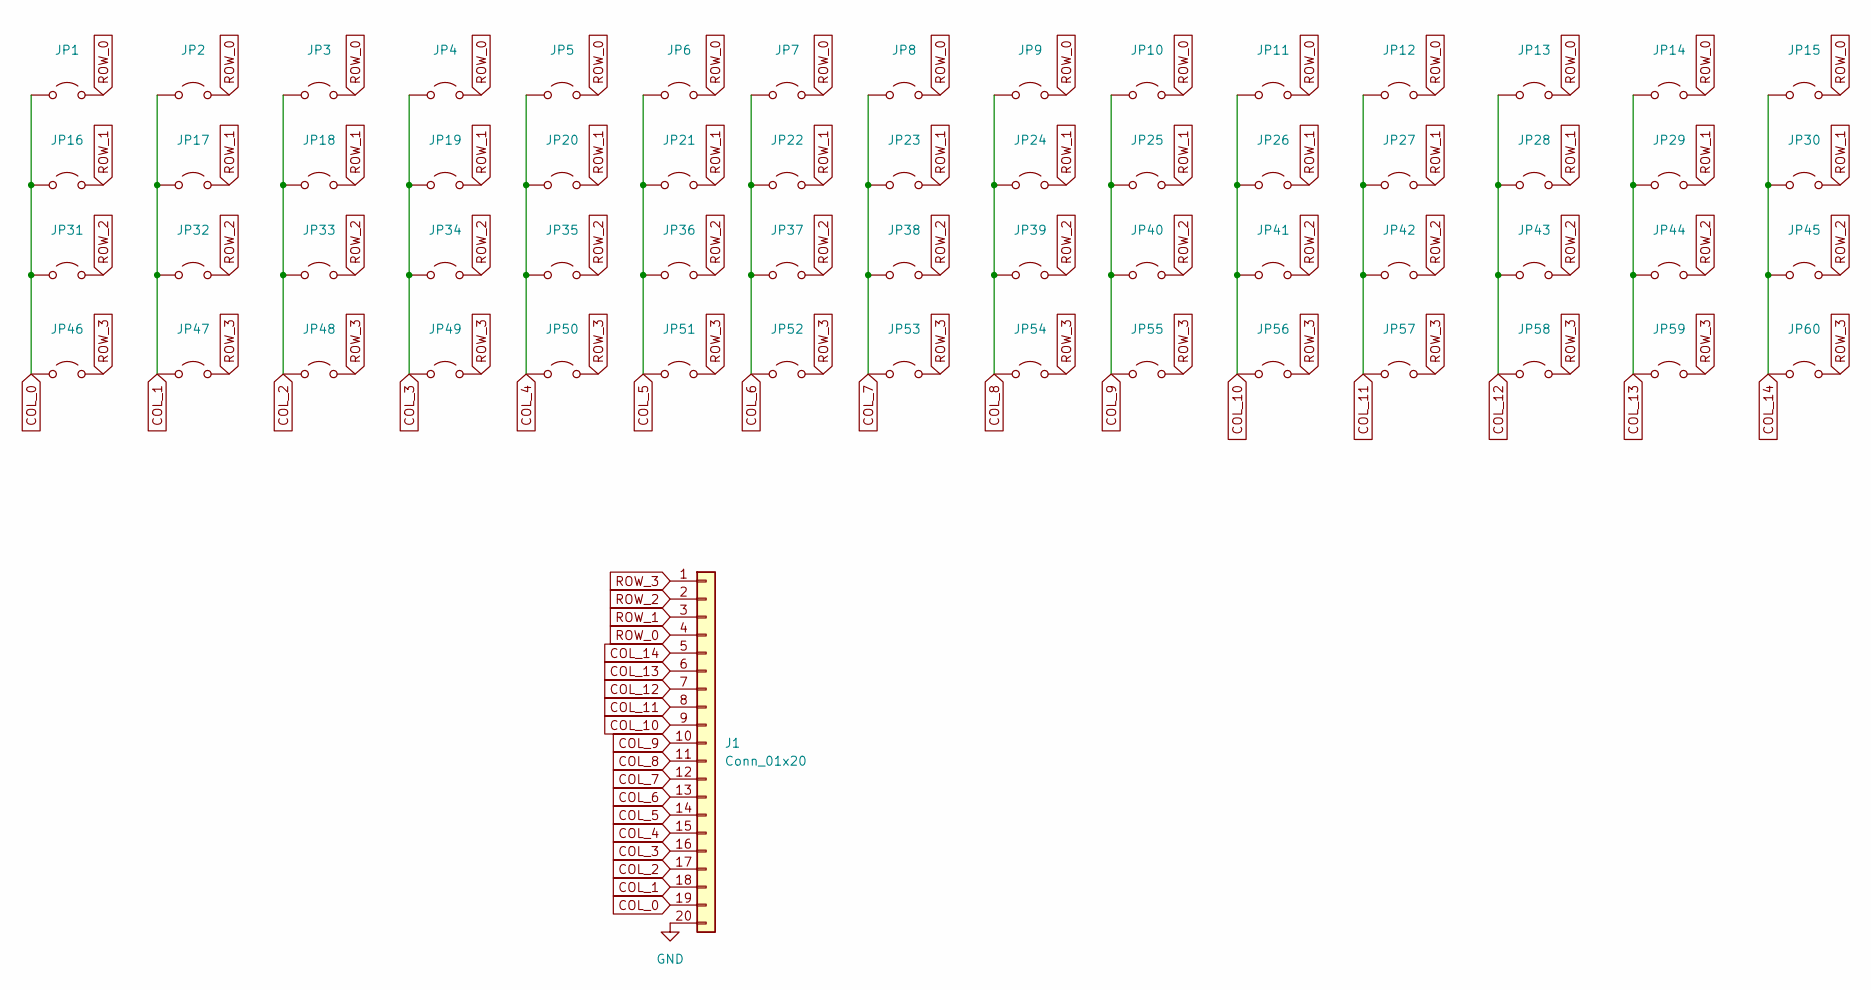
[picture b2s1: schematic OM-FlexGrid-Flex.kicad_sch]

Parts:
J1: Conn_01x20; 20Pin-FFC
JP1, JP2, JP3, JP4, JP5, JP6, JP7, JP8, JP9, JP10, JP11, JP12, JP13, JP14, JP15, JP16, JP17, JP18, JP19, JP20, JP21, JP22, JP23, JP24, JP25, JP26, JP27, JP28, JP29, JP30, JP31, JP32, JP33, JP34, JP35, JP36, JP37, JP38, JP39, JP40, JP41, JP42, JP43, JP44, JP45, JP46, JP47, JP48, JP49, JP50, JP51, JP52, JP53, JP54, JP55, JP56, JP57, JP58, JP59, JP60: Jumper_2_Open; 10mmPad

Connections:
COL_0: J1.19, JP1.1 (A), JP16.1 (A), JP31.1 (A), JP46.1 (A)
COL_1: J1.18, JP2.1 (A), JP17.1 (A), JP32.1 (A), JP47.1 (A)
COL_2: J1.17, JP3.1 (A), JP18.1 (A), JP33.1 (A), JP48.1 (A)
COL_3: J1.16, JP4.1 (A), JP19.1 (A), JP34.1 (A), JP49.1 (A)
COL_4: J1.15, JP5.1 (A), JP20.1 (A), JP35.1 (A), JP50.1 (A)
COL_5: J1.14, JP6.1 (A), JP21.1 (A), JP36.1 (A), JP51.1 (A)
COL_6: J1.13, JP7.1 (A), JP22.1 (A), JP37.1 (A), JP52.1 (A)
COL_7: J1.12, JP8.1 (A), JP23.1 (A), JP38.1 (A), JP53.1 (A)
COL_8: J1.11, JP9.1 (A), JP24.1 (A), JP39.1 (A), JP54.1 (A)
COL_9: J1.10, JP10.1 (A), JP25.1 (A), JP40.1 (A), JP55.1 (A)
COL_10: J1.9, JP11.1 (A), JP26.1 (A), JP41.1 (A), JP56.1 (A)
COL_11: J1.8, JP12.1 (A), JP27.1 (A), JP42.1 (A), JP57.1 (A)
COL_12: J1.7, JP13.1 (A), JP28.1 (A), JP43.1 (A), JP58.1 (A)
COL_13: J1.6, JP14.1 (A), JP29.1 (A), JP44.1 (A), JP59.1 (A)
COL_14: J1.5, JP15.1 (A), JP30.1 (A), JP45.1 (A), JP60.1 (A)
GND: J1.20
ROW_0: J1.4, JP1.2 (B), JP2.2 (B), JP3.2 (B), JP4.2 (B), JP5.2 (B), JP6.2 (B), JP7.2 (B), JP8.2 (B), JP9.2 (B), JP10.2 (B), JP11.2 (B), JP12.2 (B), JP13.2 (B), JP14.2 (B), JP15.2 (B)
ROW_1: J1.3, JP16.2 (B), JP17.2 (B), JP18.2 (B), JP19.2 (B), JP20.2 (B), JP21.2 (B), JP22.2 (B), JP23.2 (B), JP24.2 (B), JP25.2 (B), JP26.2 (B), JP27.2 (B), JP28.2 (B), JP29.2 (B), JP30.2 (B)
ROW_2: J1.2, JP31.2 (B), JP32.2 (B), JP33.2 (B), JP34.2 (B), JP35.2 (B), JP36.2 (B), JP37.2 (B), JP38.2 (B), JP39.2 (B), JP40.2 (B), JP41.2 (B), JP42.2 (B), JP43.2 (B), JP44.2 (B), JP45.2 (B)
ROW_3: J1.1, JP46.2 (B), JP47.2 (B), JP48.2 (B), JP49.2 (B), JP50.2 (B), JP51.2 (B), JP52.2 (B), JP53.2 (B), JP54.2 (B), JP55.2 (B), JP56.2 (B), JP57.2 (B), JP58.2 (B), JP59.2 (B), JP60.2 (B)

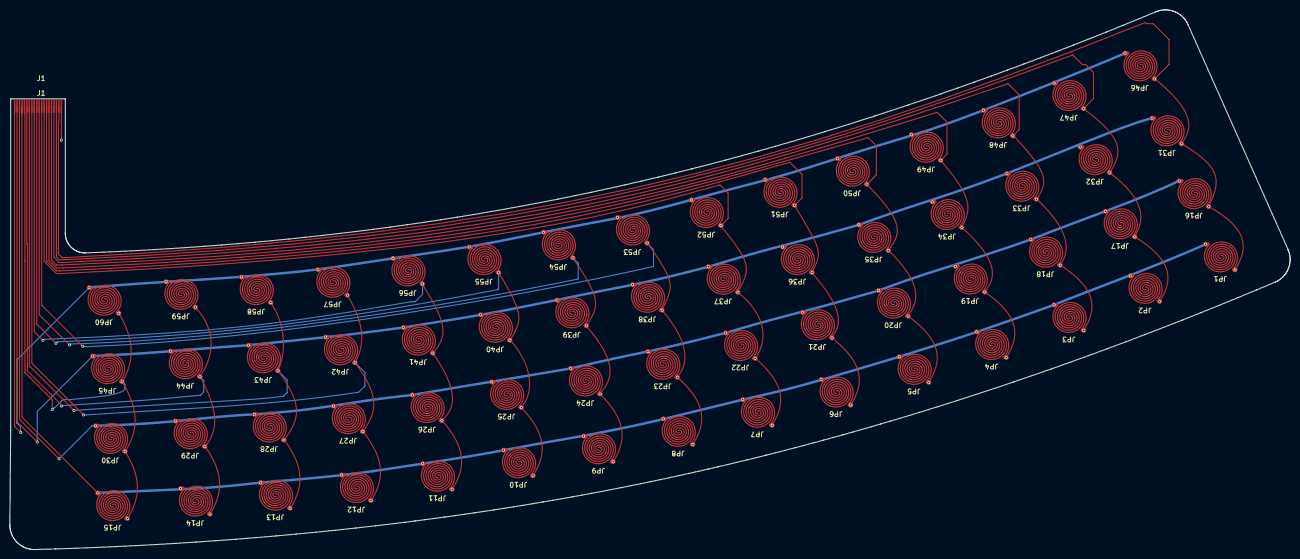
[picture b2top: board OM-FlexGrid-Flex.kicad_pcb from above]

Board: 2 copper layers, 260.0 x 109.6 mm, 61 parts (0 on the bottom side), 19 nets.

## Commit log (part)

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2025-05-24 Readme
2025-05-30 FlexGrid V1 Adjustments
2025-06-18 FlexGrid V1
2025-06-18 FlexGridV1
2025-07-05 V1-1
2025-12-19 Hardware Tweaks
2026-02-06 Cleanup V2-1
2026-02-06 Add .gitignore and exclude CLAUDE.md from tracking
2026-02-06 V2 README
2026-02-26 V2-1
2026-04-26 V3 release - 20-pin FFC interconnect (ordered, untested)
    - Switch flex-to-rigid interconnect to Wurth 687120183722 ZIF FFC
    - Integrated stiffened FFC tail on flex (FR4, 0.20 mm, bottom side)
    - Widen FFC tail to 11.1 mm to meet Wurth 0.8 mm side margin spec
    - Add V3 gerber bundles (flex + rigid), rigid BOM CSV, V3 schematic PDF
    - Update top-level README to highlight V3 as latest revision
    - Rename schematic PDFs: Rigit -> Rigid
2026-05-13 V3 bring-up complete (2026-05-13)
    Two V3 boards populated and tested end-to-end. Wurth 687120183722 FFC
    interconnect mates cleanly with the integrated stiffened flex tail
    (0.20 mm FR4 stiffener, bottom side, ~0.31 mm total -- on Wurth's
    0.30+/-0.05 mm spec). Sensor matrix scans at ~140 Hz with clean idle
    baseline and no row-sneak crosstalk (firmware fix: ground-other-rows
    scan technique). UDP telemetry confirmed reaching the desktop.
2026-05-14 V3 README: bring-up findings + design suggestions for V4
    Document the five firmware-fixable issues we hit during V3 bring-up
    and the one open hardware finding (IO2/ROW_1 won't drive HIGH on
    board #1). Add a V4 design-suggestions section: per-row series R,
    ADC GPIO selection notes, BOOT button placement, per-cell Velostat
    patches, FFC pin-1 silkscreen markers, and test pads. None are
    required -- V3 works -- but they'd save bring-up time on the next
2026-05-14 V3 status: PRODUCTION-QUALITY MATRIX
    v0.1.7 firmware now delivers clean single-cell press detection across
    all 60 sensors. 22% per-col carryover, decaying to noise within 3 cols.
    Direct press peak ~1100 ADC counts, idle baseline 0, scan rate 59 Hz.
    Verified with 45-cell deliberate per-cell press test (capture 1778731003).
    For the first time in the project's history, the FlexGrid matrix is
    usable as a real ML training data source. The V3 hardware revision
2026-05-30 V4: baseline copy from V3, fab/backup/cache artifacts cleaned
    Starting point for V4 hardware revision. Schematically + topologically
    identical to V3 at the moment of this commit so that any subsequent V4
    commit shows up cleanly as a diff against this baseline. V3 hardware
    stays canonical for currently-fielded boards and is not modified.
    What was carried forward:
    - OM-FlexGrid-Flex/ KiCad project (sch, pcb, pro)
2026-06-07 V4 progress: SD card reader, RGB status LED, slimmer reoriented layout
    What landed in V4 (Rigid PCB):
    - microSD card socket added (data logging / model storage on-device)
    - Discrete RGB status LED (5050 common-cathode driven by 3 PWM GPIOs,
    zero quiescent current vs WS2812 family; status palette ready to
    drive from firmware)
    - Board orientation flipped for a slimmer profile that hugs the
2026-06-07 V4 documentation: revision README, JLCPCB workflow, cross-version status
    Three docs land together so V4 has a real introduction for anyone
    walking up to the repo cold (future-self included):
    KiCad/OM-FlexGrid V4/README.md (replaces the V3 carryover)
    Status block, V4-vs-V3 change table, microSD wiring + part, RGB LED
    wiring + suggested status palette, layout reorientation rationale,
    footprint cleanup notes (SOD-123 standardization, 0603 enforcement),
2026-06-07 V4 README: lock in fab strategy + complete hand-solder list
    Updates the V4 README to reflect actual decisions made during the
    final BOM pass:
    - Status bumped from "IN DESIGN" to "READY FOR FAB" with the explicit
    10-unit batch + single-side SMT + hand assembly strategy stated up
    front so anyone reading the repo cold sees the plan in one block.
    - Manufacturing section grew a "Strategy" subsection explaining the
2026-06-07 V4 README: document haptic + ADC matrix caps as untested carry-forwards
    Two known concerns from the V3 bring-up history are now explicitly
    called out so a future bring-up cannot miss them:
    1. Haptic feedback circuit. Carried forward from V3 as a "just in
    case" feature. Built but never bench-tested in this configuration.
    Documented as optional / experimental, with a firmware note that
    the haptic GPIO should default low and only fire behind explicit
2026-06-07 V4 rev: ADC matrix caps 2.2uF -> 100pF, MAX16054 footprint TSOT-23-6
    Two real design changes applied to the V4 Rigid PCB this revision:
    1. ADC matrix-row caps C12, C13, C14, C15 changed from 2.2 uF
    to 100 pF. This is Option 3 from the README's "Known carry-forward
    concerns" section. New LCSC: C14858 (100 pF 0603, Basic tier).
    RC time constant with the 10 kohm row pulldown drops from ~22 ms
    to ~1 us, well below the per-column ADC dwell time. Resolves the
2026-06-07 V4 README: mark ADC cap decision + MAX16054 footprint swap as resolved
    Reflects the design changes that just landed in a8c1de1:
    - ADC matrix-row caps section is now RESOLVED at 100 pF (LCSC
    C14858). Three-option analysis preserved for posterity but the
    choice is explicit. The "decide C12-C15 fate" item is removed
    from the still-open checklist.
    - Footprint cleanup list gains the MAX1 (MAX16054) SOT-23-6 ->
2026-06-07 V4 README: drop accidental em dash in resolved-caps header
    Style cleanup. The repo's documentation policy is no em dashes;
    the previous commit slipped one into a new section header.
    Replaced with a colon.
2026-06-07 V4 Flex: Fusion 360 -> KiCad SVG prep script + ready-to-import outlines
    Two Fusion 360 / Shaper Origin exports needed shape massaging before
    they could go into KiCad on the right layers:
    FFC-Stiffener_Faces.svg 1.2 x 0.8 cm rectangle, stiffener for
    the FFC tail
    V4CurveCutout_Faces.svg ~10.8 x 28.3 cm curved outline of the
    entire flex PCB body
2026-06-07 V4 Flex: cutout rotated +67.6 deg to match horizontal-bracelet layout
    User feedback: my auto-rotation laid the banana shape on its vertical
    axis (28cm tall, 10cm wide), but the actual target orientation is
    horizontal -- body lying on its side, FFC tail at bottom-left, body
    curving up to the right end. That matches how the flex actually wraps
    around the user's forearm in the bracelet form factor.
    Re-ran prep_flex_svgs.py with --rotate-cutout 67.615 (which is
2026-06-07 V4 Flex: pick up new Fusion export with 10.5mm FFC tail width
    User re-exported from Fusion 360 after fixing the FFC tail width
    from 11.1mm to 10.5mm (the correct value per the Wurth 687120183722
    datasheet). The new export landed as FFC-Stiffener.svg and
    V4CurveCutout.svg (without the _Faces suffix Fusion was using
    before).
    Script change: prep_flex_svgs.py now prefers the non-suffixed
2026-06-09 top README: surface V4 in-development status + cross-revision links
    Brings the repo landing page in line with the V4 work that just
    landed publicly:
    - Header gets a second status badge for V4 (in development) alongside
    the existing V3 (stable) badge.
    - "Latest revision" section becomes "Current revisions" with V4 and
    V3 blocks side by side. V4 block summarizes what's new (microSD,
2026-06-09 V4 README: link reviewable PDFs + 5 PDF files added
    User asked to make the schematic and PCB PDFs discoverable from the
    V4 README so people can review the design without opening KiCad.
    Adds a "Design documents (PDFs)" section near the top of the README,
    right after the status block, with click-through links to:
    Rigid PCB:
    FlexGridV4-Rigid-Schematic.pdf full schematic, all sheets
2026-06-09 Add FlexGrid V4 design with onboard SD card; clean up backups
    V4 rigid and flex PCB design. Adds an onboard microSD card so the band can log capture sessions standalone, without a tethered PC. V4 3D and animation assets (Blender, glTF, STEP) are tracked via Git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
    Also stop versioning KiCad and Blender auto-backups (*-backups/, *.blend[0-9]) and remove the old backup archives.
    Suggested-by: Kyle.T.Y <64039282+HeatRIderHR@users.noreply.github.com>
2026-06-09 Add CERN-OHL-S-2.0 license text at repo root
    The README already declared CERN-OHL-S-2.0 but GitHub license detection
    needs the text in a root LICENSE file.
2026-06-12 V4 ordered: as-fabricated state + cost breakdown in README
    Submitted 10 units to JLCPCB on 2026-06-12 for single-side SMT.
    Total landed cost $341.84 ($34/board JLC + ~$12/board hand-solder
    add-ons). Captures the as-ordered KiCad files and the generated
    flex Gerber set so future revisions can diff cleanly against what
    the first 10 physical boards came from.
    README:
2026-06-23 V4 Rigid PCB: fix USBLC6 pinout + expand JLC-assembled BOM
    USBLC6 ESD chip fix
    -------------------
    Swap the VBUS and GND power-flag connections on the USBLC6-2SC6
    footprint in the schematic. Earlier revision wired pin 2 to VBUS
    and pin 5 to GND, but the actual chip pinout is pin 2 = GND and
    pin 5 = VCC. Result on the first populated V4 board was that the
2026-06-24 docs(V4): refresh README to reflect bring-up state
    V4 boards arrived 2026-06-23 and are running V4 firmware end-to-end.
    README was still saying 'In fab at JLCPCB. Not yet brought up.'
    Updates:
    - Top status block now reads BROUGHT UP 2026-06-23, summarizes the
    two HW bugs found during bring-up.
    - New 'Bring-up findings' section covers the USBLC6 pinout reversal
2026-06-24 docs(V4): add build video link to the README
    Link the Unboxing & Setup video (hand-assembly + bring-up) from the V4 README.

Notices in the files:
KiCad/OM-FlexGrid V3/README.md:
Hardware released under **CERN Open Hardware License v2.0 (CERN-OHL-S-2.0)**.
README.md:
License: CERN-OHL-S-2.0
parts and their libraries:
Copyright 2016 Accelerated Designs. All rights reserved.
